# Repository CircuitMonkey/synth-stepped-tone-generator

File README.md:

# synth-stepped-tone-generator
Sound synthesizer circuit for stepped tones. Based on a Forest Mimms III circuit design.

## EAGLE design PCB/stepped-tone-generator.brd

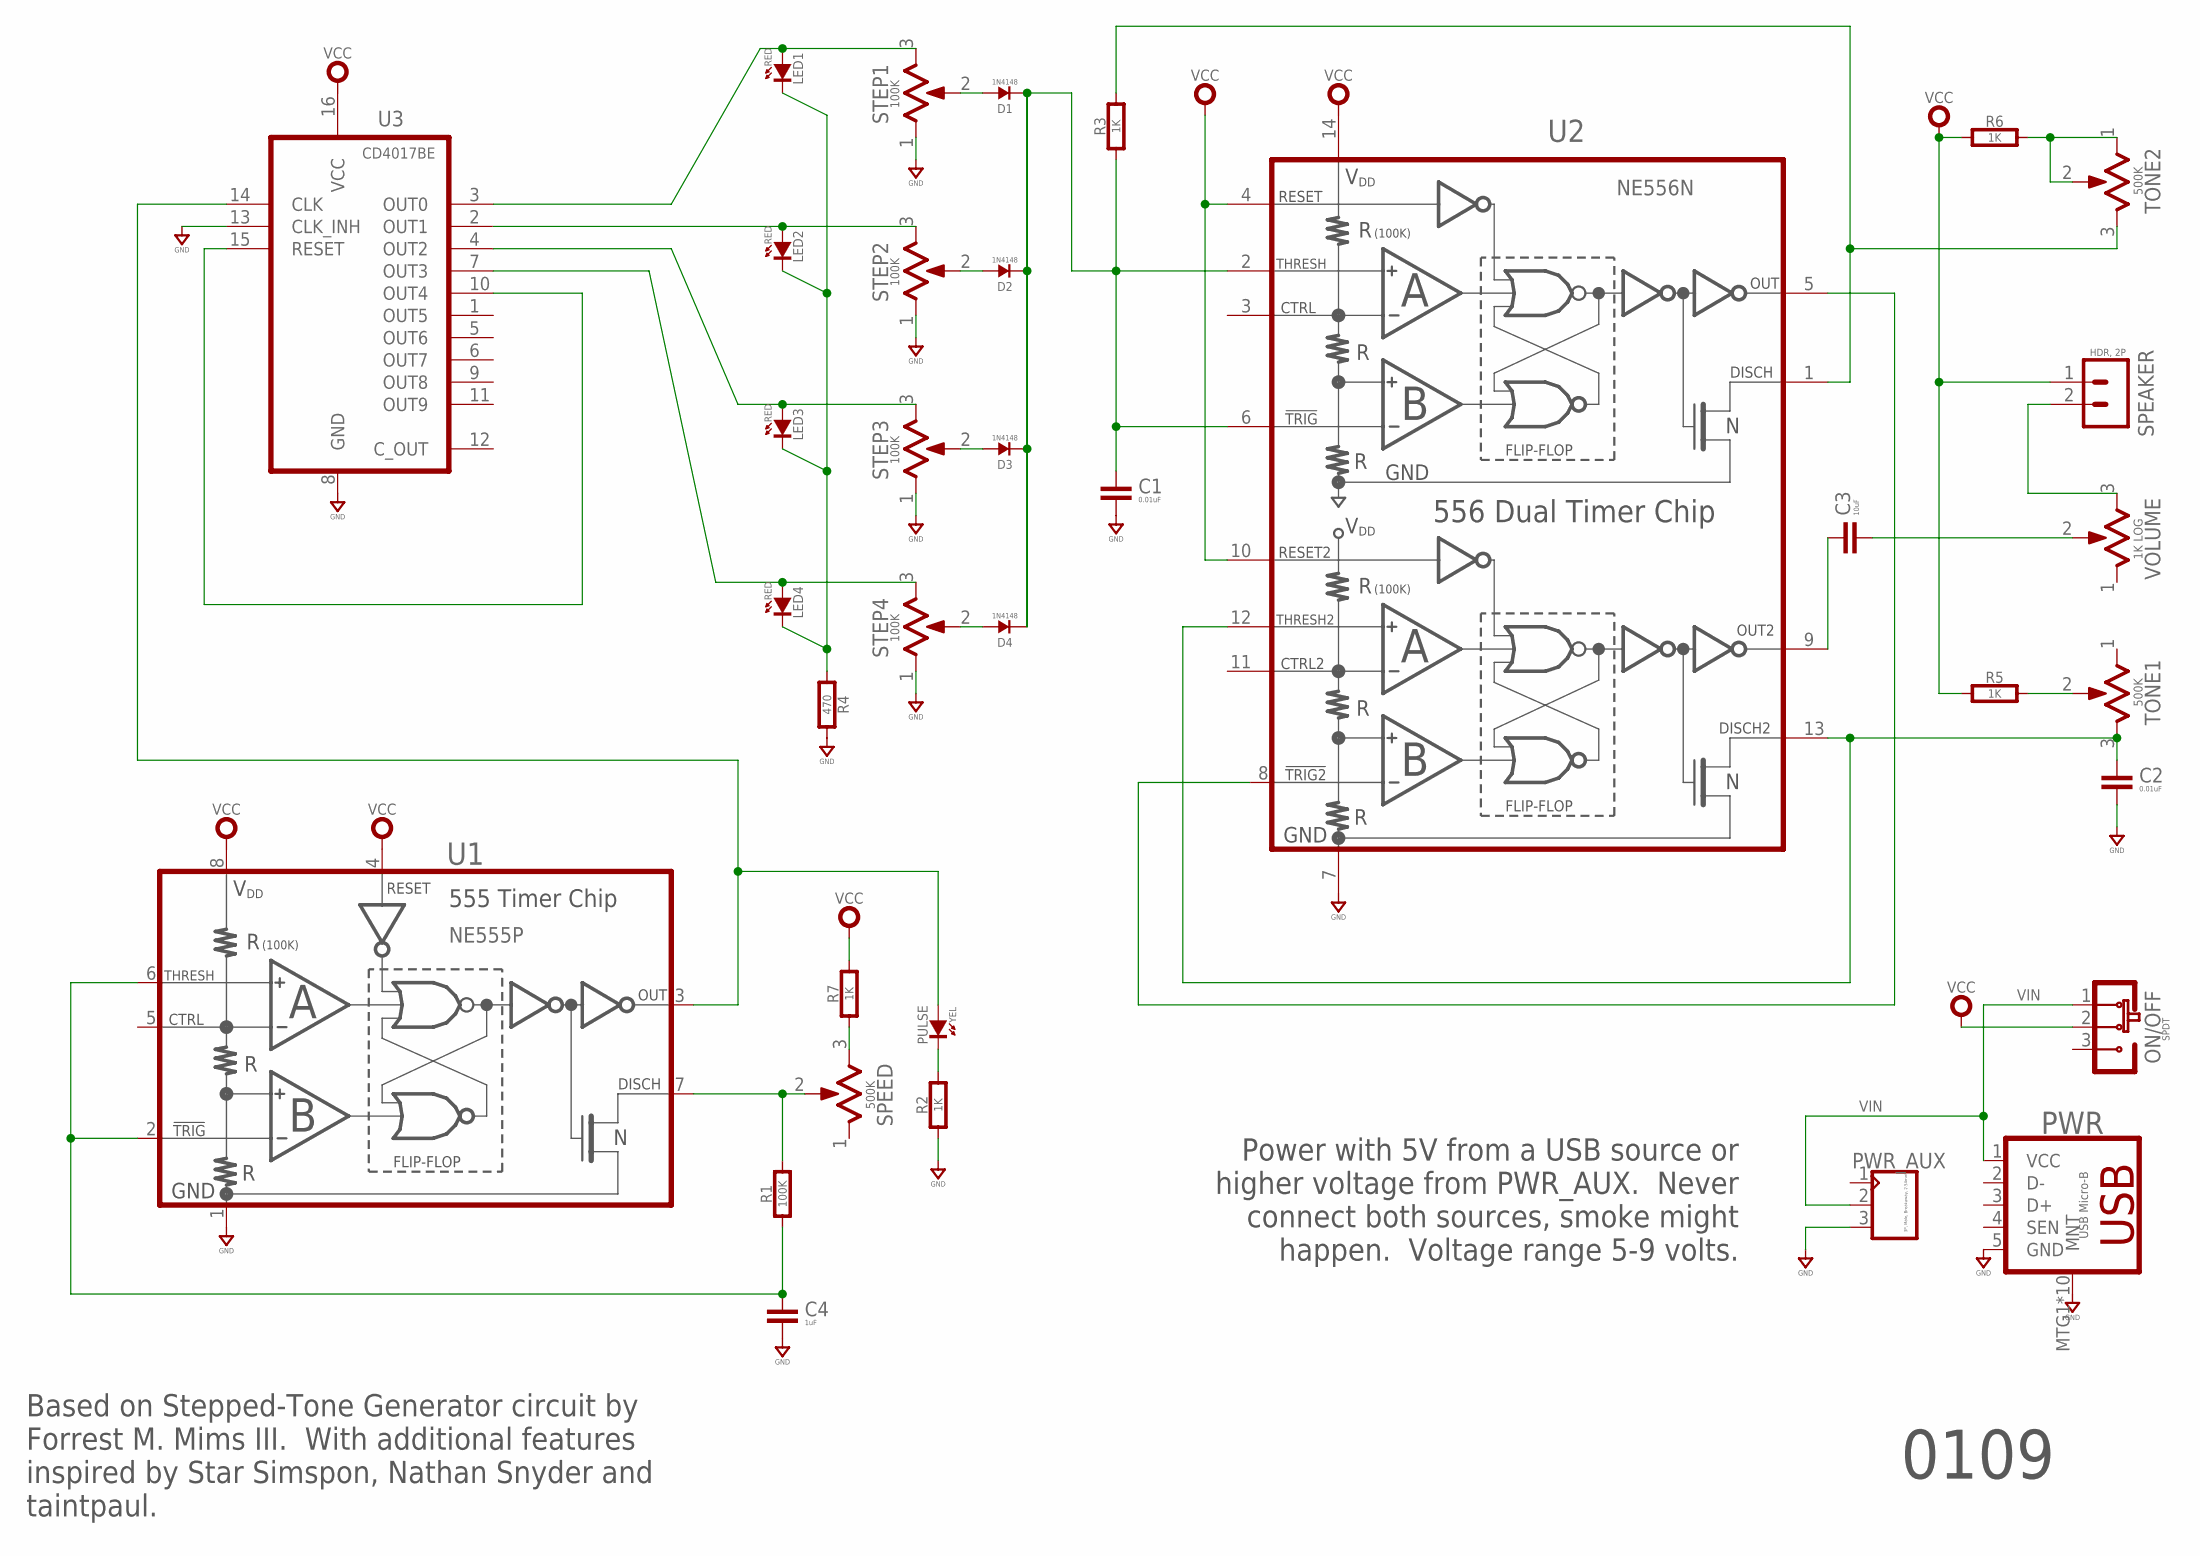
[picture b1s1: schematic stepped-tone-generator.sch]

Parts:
C1, C2: 0.01uF; CAP_CER_THD_5MM
C3: 10uF; CAP_CER_THD_5MM
C4: 1uF; CAP_CER_THD_5MM
D1, D2, D3, D4: 1N4148; DO-35(THD)
LED1, LED2, LED3, LED4: RED; THD_3MM
ON/OFF: SPDT; MTS-102
PULSE: YEL; THD_3MM
PWR: USB Micro-B; JAE-DX4R005
PWR_AUX: 3P, Male, Breakaway, 2.54mm; MA03X1-VT-THD
R1: 100K; R_THD_0.25W
R2, R3, R5, R6, R7: 1K; R_THD_0.25W
R4: 470; R_THD_0.25W
SPEAKER: HDR, 2P; MA02-1-FAT
SPEED: 500K; ALPS_RK09D113
STEP1, STEP2, STEP3, STEP4: 100K; ALPS_RK09D113
TONE1, TONE2: 500K; ALPS_RK09D113
U1: NE555P; DIP-08
U2: NE556N; DIP-14
U3: CD4017BE; DIP-16
VOLUME: 1K LOG; ALPS_RK09D113

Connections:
GND: C1.2, C2.2, C4.2, PWR.5 (GND), PWR.MTG1 (MNT), PWR.MTG2 (MNT), PWR.MTG3 (MNT), PWR.MTG4 (MNT), PWR.MTG5 (MNT), PWR.MTG6 (MNT), PWR.MTG7 (MNT), PWR.MTG8 (MNT), PWR.MTG9 (MNT), PWR.MTG10 (MNT), PWR_AUX.3, R2.1, R4.1, SPEED.MT1A (GND), SPEED.MT1B (GND), SPEED.MT1C (GND), SPEED.MT2A (GND), SPEED.MT2B (GND), SPEED.MT2C (GND), STEP1.1, STEP1.MT1A (GND), STEP1.MT1B (GND), STEP1.MT1C (GND), STEP1.MT2A (GND), STEP1.MT2B (GND), STEP1.MT2C (GND), STEP2.1, STEP2.MT1A (GND), STEP2.MT1B (GND), STEP2.MT1C (GND), STEP2.MT2A (GND), STEP2.MT2B (GND), STEP2.MT2C (GND), STEP3.1, STEP3.MT1A (GND), STEP3.MT1B (GND), STEP3.MT1C (GND), STEP3.MT2A (GND), STEP3.MT2B (GND), STEP3.MT2C (GND), STEP4.1, STEP4.MT1A (GND), STEP4.MT1B (GND), STEP4.MT1C (GND), STEP4.MT2A (GND), STEP4.MT2B (GND), STEP4.MT2C (GND), TONE1.MT1A (GND), TONE1.MT1B (GND), TONE1.MT1C (GND), TONE1.MT2A (GND), TONE1.MT2B (GND), TONE1.MT2C (GND), TONE2.MT1A (GND), TONE2.MT1B (GND), TONE2.MT1C (GND), TONE2.MT2A (GND), TONE2.MT2B (GND), TONE2.MT2C (GND), U1.1 (GND), U2.7 (GND), U3.8 (GND), U3.13 (CLK_INH), VOLUME.MT1A (GND), VOLUME.MT1B (GND), VOLUME.MT1C (GND), VOLUME.MT2A (GND), VOLUME.MT2B (GND), VOLUME.MT2C (GND)
unnamed: PULSE.A, U1.3 (OUTPUT), U3.14 (CLK)
unnamed: U3.10 (OUT4), U3.15 (RESET)
unnamed: LED1.A, STEP1.3, U3.3 (OUT0)
unnamed: LED2.A, STEP2.3, U3.2 (OUT1)
unnamed: LED3.A, STEP3.3, U3.4 (OUT2)
unnamed: LED4.A, STEP4.3, U3.7 (OUT3)
unnamed: R5.2, TONE1.2
unnamed: R3.2, TONE2.3, U2.1 (DISCHARGE)
unnamed: C3.1, U2.9 (OUTPUT2)
unnamed: C2.1, TONE1.3, U2.12 (THRESHOLD2), U2.13 (DISCHARGE2)
unnamed: U2.5 (OUTPUT), U2.8 (TRIGGER2#)
unnamed: C4.1, R1.1, U1.2 (TRIGGER#), U1.6 (THRESHOLD)
unnamed: LED1.K (C), LED2.K (C), LED3.K (C), LED4.K (C), R4.2
unnamed: R1.2, SPEED.2, U1.7 (DISCHARGE)
unnamed: PULSE.K (C), R2.2
unnamed: D1.A, STEP1.2
unnamed: D2.A, STEP2.2
unnamed: D3.A, STEP3.2
unnamed: D4.A, STEP4.2
unnamed: C1.1, D1.K, D2.K, D3.K, D4.K, R3.1, U2.2 (THRESHOLD), U2.6 (TRIGGER#)
unnamed: C3.2, VOLUME.2
unnamed: R7.1, SPEED.3
unnamed: R6.2, TONE2.1, TONE2.2
unnamed: SPEAKER.2, VOLUME.3
VCC: ON/OFF.2, R5.1, R6.1, R7.2, SPEAKER.1, U1.4 (RESET#), U1.8 (VDD), U2.4 (RESET#), U2.10 (RESET2), U2.14 (VDD), U3.16 (VCC)
VIN: ON/OFF.1, PWR.1 (VCC), PWR_AUX.2

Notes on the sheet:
Based on Stepped-Tone Generator circuit by Forrest M. Mims III. With additional features inspired by Star Simspon, Nathan Snyder and taintpaul.
Power with 5V from a USB source or higher voltage from PWR_AUX. Never connect both sources, smoke might happen. Voltage range 5-9 volts.
0109

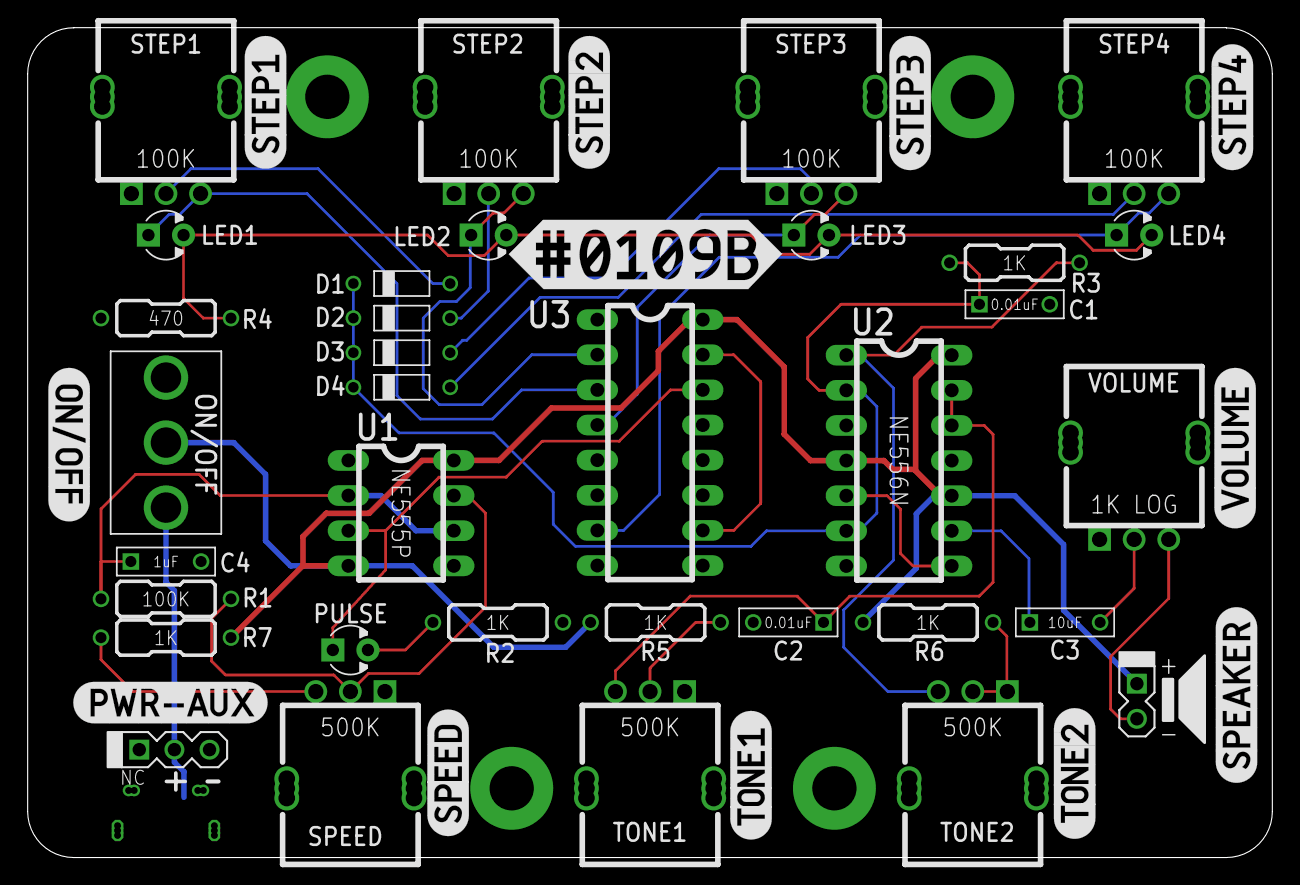
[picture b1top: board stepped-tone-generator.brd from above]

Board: 2 copper layers, 90.0 x 60.0 mm, 35 parts (1 on the bottom side), 27 nets.

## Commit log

2021-01-31 Rev. A
2021-03-18 Update stepped-tone-generator.ods
    Update BOM
2021-03-21 Made PCB larger. Set proper values for pots.
2021-03-22 Added labels for pots.
2021-07-29 Stepped tone generator fixes
